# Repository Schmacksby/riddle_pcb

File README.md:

# electro-maschine.com
## Riddle PCB
This PCB is part of an semi-online riddle. This PCB is needed to solve the riddles shown on the website.

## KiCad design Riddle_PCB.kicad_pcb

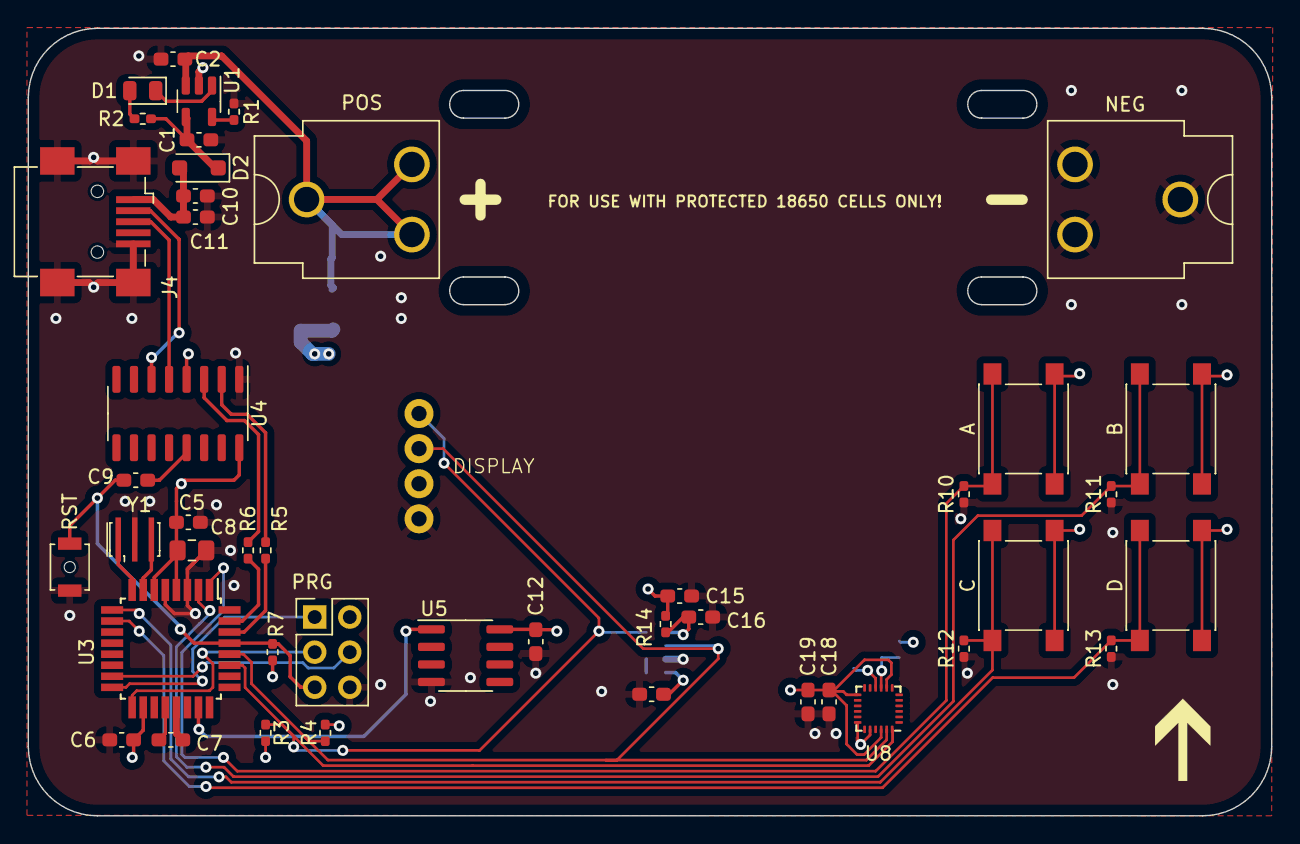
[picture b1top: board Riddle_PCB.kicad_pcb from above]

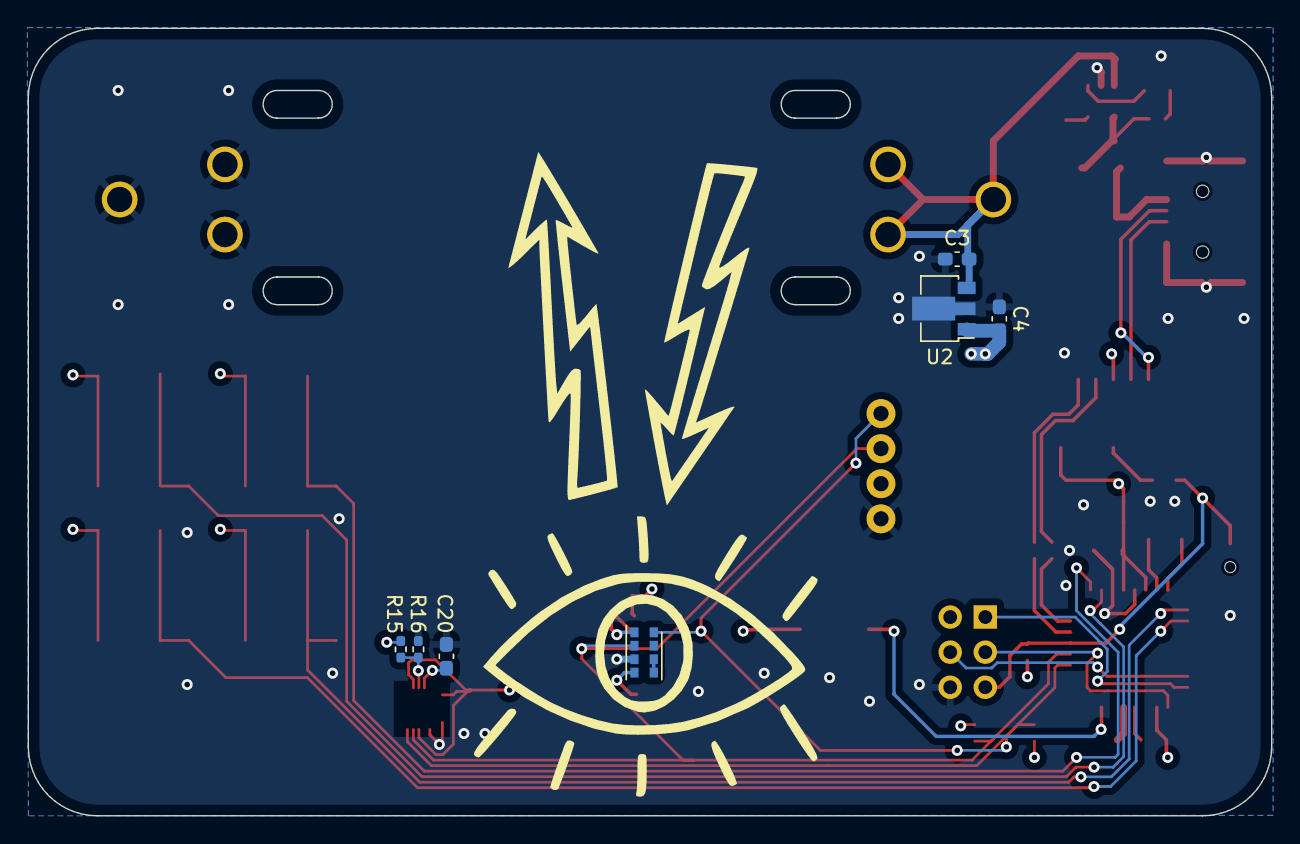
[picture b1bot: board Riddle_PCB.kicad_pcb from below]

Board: 4 copper layers, 90.0 x 57.0 mm, 52 parts (7 on the bottom side), 33 nets.

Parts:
A: SW_Push; SW_SPST_PTS645
B: SW_Push; SW_SPST_PTS645
C: SW_Push; SW_SPST_PTS645
C1, C2: 4u7; C_0603_1608Metric_Pad1.08x0.95mm_HandSolder
C3, C5, C6, C16, C17: 1u; C_0603_1608Metric_Pad1.08x0.95mm_HandSolder
C4, C10, C15: 10u; C_0603_1608Metric_Pad1.08x0.95mm_HandSolder
C7, C9, C11, C12, C18, C19, C20: 100n; C_0603_1608Metric_Pad1.08x0.95mm_HandSolder
C8: 4u7/16V; C_0805_2012Metric_Pad1.18x1.45mm_HandSolder
D: SW_Push; SW_SPST_PTS645
D1: BLUE; LED_0805_2012Metric
D2: PMEG2005EH; D_SOD-123F
DISPLAY: Display; SSD1306 128x32px
J4: USB_B_Mini; USB_Mini-B_Wuerth_65100516121_Horizontal
NEG: Bat_neg; BatteryClip_Keystone_54_D16-19mm
POS: Bat_pos; BatteryClip_Keystone_54_D16-19mm
PRG: ICSP; PinHeader_2x03_P2.54mm_Vertical
R1: 2k; R_0402_1005Metric_Pad0.72x0.64mm_HandSolder
R2: 470R; R_0402_1005Metric_Pad0.72x0.64mm_HandSolder
R3, R4: 4k7; R_0402_1005Metric_Pad0.72x0.64mm_HandSolder
R5, R6, R7: 1k; R_0402_1005Metric_Pad0.72x0.64mm_HandSolder
R10, R11, R12, R13: 10k; R_0402_1005Metric_Pad0.72x0.64mm_HandSolder
R14: 22R; R_0402_1005Metric_Pad0.72x0.64mm_HandSolder
R15: 0R; R_0402_1005Metric_Pad0.72x0.64mm_HandSolder
R16: dnp; R_0402_1005Metric_Pad0.72x0.64mm_HandSolder
RST: RESET_JMP; SW_SPST_B3U-1000P-B
U1: MCP73831-2-OT; SOT-23-5
U2: AP130-33Y; SOT-89-3
U3: ATmega328P-A; TQFP-32_7x7mm_P0.8mm
U4: CH340C; SOIC-16_3.9x9.9mm_P1.27mm
U5: TMP36xS; SOIC-8_3.9x4.9mm_P1.27mm
U7: APDS-9960; Avago_APDS-9960
U8: ICM-20948; InvenSense_QFN-24_3x3mm_P0.4mm
Y1: Resonator 8MHz; Resonator_SMD_Murata_CSTxExxV-3Pin_3.0x1.1mm_HandSoldering

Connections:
/3V3: A.2, B.2, C.2, C4.1, C5.1, C6.1, C8.1, C12.1, C15.1, C17.1, C18.1, C19.1, D.2, DISPLAY.3, PRG.2, R3.2, R4.2, R7.2, R14.1, R15.1, U2.1 (VO), U3.4 (VCC), U3.6 (VCC), U3.18 (AVCC), U4.4 (V3), U4.16 (VCC), U5.8 (+Vs), U7.5 (LED_A), U8.8 (VDDIO), U8.13 (VDD), U8.22 (~CS)
/Microcontroller/MISO: PRG.1, U3.16 (PB4)
/Microcontroller/MOSI: PRG.4, U3.15 (PB3)
/Microcontroller/RESET: C9.1, PRG.5, R7.1, RST.2 (B), U3.29 (~RESET/PC6)
/Microcontroller/RX/PD0: R5.1, U3.30 (PD0)
/Microcontroller/SCK: PRG.3, U3.17 (PB5)
/Microcontroller/TX/PD1: R6.1, U3.31 (PD1)
/Powersupply/Bat_pos: C2.1, C3.1, POS.1, U1.3 (V_{BAT}), U2.3 (VI)
/Powersupply/STAT: D1.1 (K), U1.1 (STAT)
/SCL: DISPLAY.2, R4.1, U3.28 (PC5), U7.7 (SCL), U8.23 (SCL/SCLK)
/SDA: DISPLAY.1, R3.1, U3.27 (PC4), U7.1 (SDA), U8.24 (SDA/SDI)
/SW1: A.1, R10.1, U3.1 (PD3)
/SW2: B.1, R11.1, U3.2 (PD4)
/SW3: C.1, R12.1, U3.9 (PD5)
/SW4: D.1, R13.1, U3.10 (PD6)
/V_BUS: C1.1, D2.1 (K), R2.2, U1.4 (V_{DD})
/analog_temp: U3.23 (PC0), U5.1 (V_{OUT})
GND: C1.2, C2.2, C3.2, C4.2, C5.2, C6.2, C7.2, C8.2, C10.2, C11.2, C12.2, C15.2, C16.2, C17.2, C18.2, C19.2, C20.2, DISPLAY.4, J4.5 (GND), J4.6 (Shield), NEG.1, PRG.6, R1.2, R10.2, R11.2, R12.2, R13.2, R16.2, RST.1 (A), U1.2 (V_{SS}), U2.2 (GND), U3.3 (GND), U3.5 (GND), U3.21 (GND), U4.1 (GND), U5.4 (GND), U7.6 (GND), U8.18 (GND), U8.20 (GND), Y1.2
unnamed: D1.2 (A), R2.1
unnamed: C10.1, C11.1, D2.2 (A), J4.1 (VBUS)
unnamed: J4.3 (D+), U4.5 (UD+)
unnamed: J4.2 (D-), U4.6 (UD-)
unnamed: R1.1, U1.5 (PROG)
unnamed: C7.1, U3.20 (AREF)
unnamed: U3.7 (XTAL1/PB6), Y1.3
unnamed: U3.8 (XTAL2/PB7), Y1.1
unnamed: R6.2, U4.3 (RXD)
unnamed: R5.2, U4.2 (TXD)
unnamed: C9.2, U4.13 (~DTR)
unnamed: U7.3 (LDR), U7.4 (LED_K)
unnamed: C16.1, R14.2, U7.8 (VCC)
unnamed: C20.1, U8.10 (REGOUT)
unnamed: R15.2, R16.1, U8.9 (SDO/AD0)

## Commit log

2024-12-04 Update README.md
    typo
